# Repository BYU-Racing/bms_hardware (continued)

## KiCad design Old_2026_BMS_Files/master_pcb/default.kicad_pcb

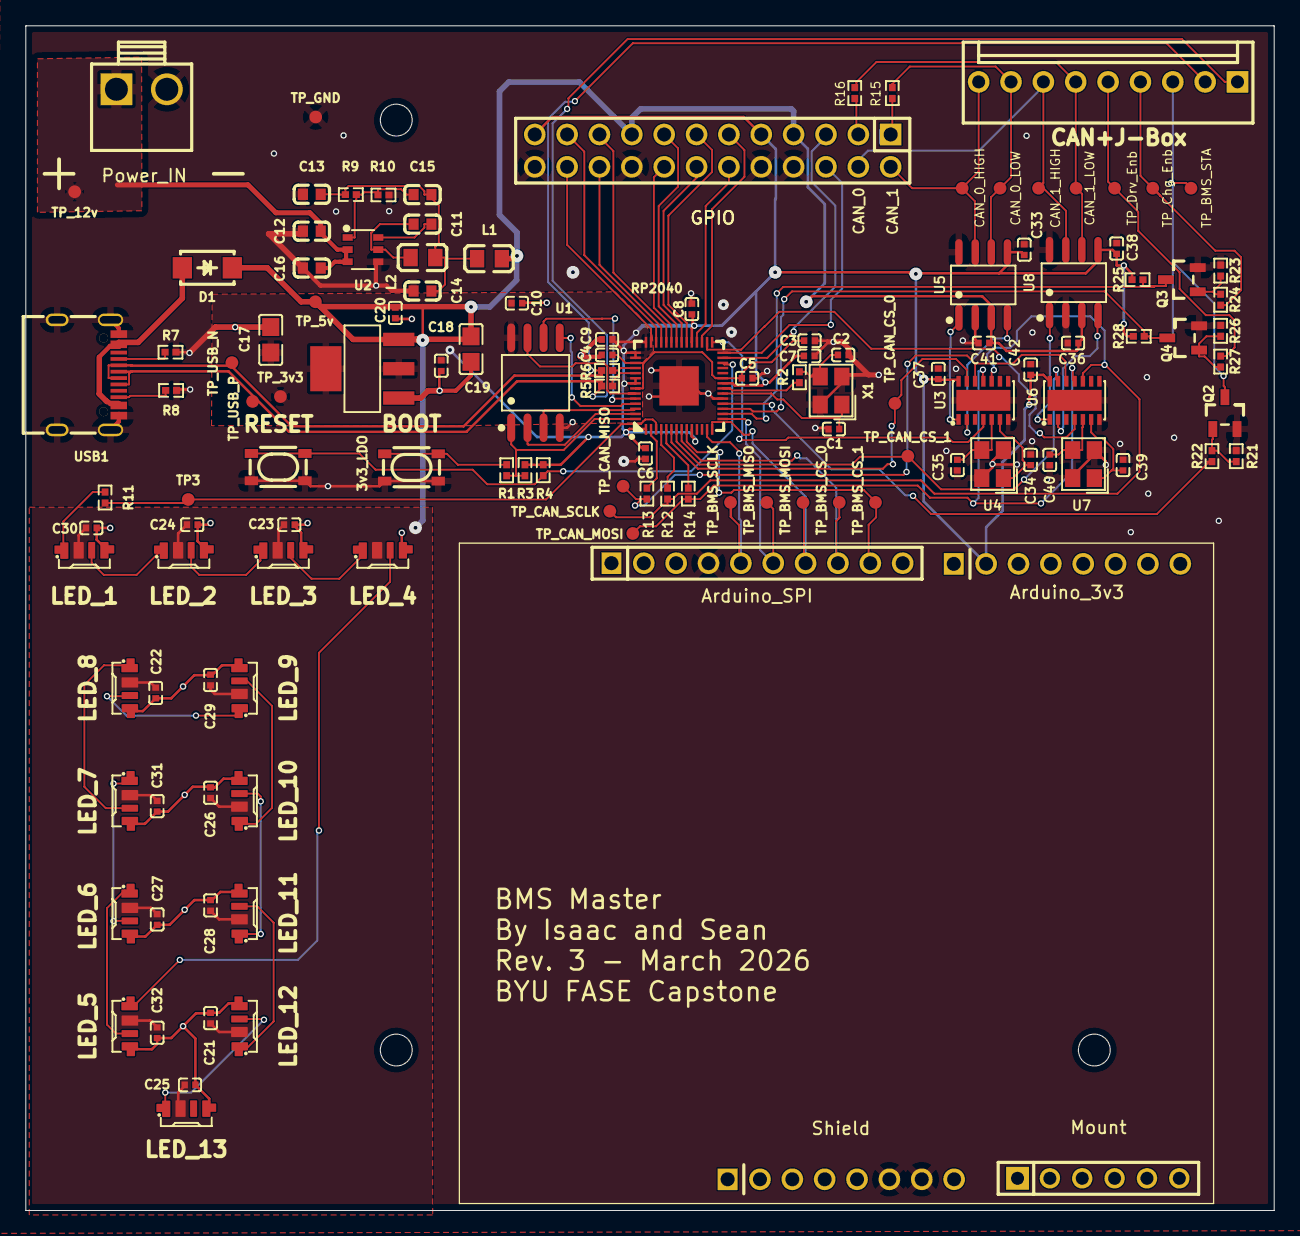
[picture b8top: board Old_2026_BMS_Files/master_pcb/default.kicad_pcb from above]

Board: 2 copper layers, 98.0 x 93.0 mm, 130 parts (0 on the bottom side), 91 nets.

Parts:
3v3_LDO: SOT-223_L6.5-W3.5-P2.30-LS7.0-BR
Arduino_3v3: HDR-TH_8P-P2.54-V-F
Arduino_SPI: HDR-TH_10P-P2.54-V-F
BOOT: KEY-SMD_4P-L4.2-W3.2-P2.20-LS4.6
C1, C2, C34, C35, C39, C40: 22pF ±5% 50V C0G; C0402
C3, C4, C5, C6, C7, C8, C9, C10: 1µF ±10% 25V X5R; C0402
C11, C16: 100nF ±10% 50V X7R; C0603
C12: 10µF ±10% 10V X5R; C0603
C13, C14: 22µF ±20% 6.3V X5R; C0603
C15: 47pF ±5% 50V C0G; C0603
C17, C19: 10µF ±10% 25V X5R; C0805
C18, C20, C21, C22, C23, C24, C25, C26, C27, C28, C29, C30, C31, C32, C33, C36, C37, C38, C41, C42: 100nF ±10% 16V X7R; C0402
CAN+J-Box: CONN-TH_9P-P2.54_MOLEX_22232091
CAN_0_HIGH, CAN_0_LOW, CAN_1_HIGH, CAN_1_LOW: TestPoint_Pad_D1.0mm
D1: SMA_L4.2-W2.6-LS5.0-RD_1
GPIO: HDR-TH_24P-P2.54-V-M-R2-C12-S2.54
L1: L0805
L2: 6.8µH ±20% 550mA 270mΩ; L0805
LED_1, LED_2, LED_3, LED_4, LED_5, LED_6, LED_7, LED_8, LED_9, LED_10, LED_11, LED_12, LED_13: LED-SMD_4P-L4.0-W1.6-L
Mount: HDR-TH_6P-P2.54-V-F
Power_IN: CONN-TH_B2P-VH-LF-SN
Q2, Q3, Q4: SOT-23-3_L2.9-W1.3-P1.90-LS2.4-TR
R1, R2: 1kΩ ±1% 62.5mW; R0402
R3, R4, R25, R28: 10kΩ ±1% 62.5mW; R0402
R5, R6: 27Ω ±1% 62.5mW; R0402
R7, R8, R22: 4.7kΩ ±1% 62.5mW; R0402
R9: 158kΩ ±1% 62.5mW; R0402
R10: 30.1kΩ ±1% 62.5mW; R0402
R11: 150Ω ±1% 62.5mW; R0402
R12, R13, R14: 22Ω ±1% 62.5mW; R0402
R15, R16: 120Ω ±1% 62.5mW; R0402
R21, R24, R27: 100kΩ ±1% 62.5mW; R0402
R23, R26: 1MΩ ±1% 62.5mW; R0402
RESET: KEY-SMD_4P-L4.2-W3.2-P2.20-LS4.6
RP2040: LQFN-56_L7.0-W7.0-P0.4-EP
Shield: HDR-TH_8P-P2.54-V-F
TP3: TestPoint_Pad_D1.0mm
TP_3v3, TP_5v, TP_12v: TestPoint_Pad_D1.0mm
TP_BMS_CS_0, TP_BMS_CS_1: TestPoint_Pad_D1.0mm
TP_BMS_MISO: TestPoint_Pad_D1.0mm
TP_BMS_MOSI: TestPoint_Pad_D1.0mm
TP_BMS_SCLK: TestPoint_Pad_D1.0mm
TP_BMS_STA: TestPoint_Pad_D1.0mm
TP_CAN_CS_0, TP_CAN_CS_1: TestPoint_Pad_D1.0mm
TP_CAN_MISO: TestPoint_Pad_D1.0mm
TP_CAN_MOSI: TestPoint_Pad_D1.0mm
TP_CAN_SCLK: TestPoint_Pad_D1.0mm
TP_Chg_Enb: TestPoint_Pad_D1.0mm
TP_Drv_Enb: TestPoint_Pad_D1.0mm
TP_GND: TestPoint_Pad_D1.0mm
TP_USB_N: TestPoint_Pad_D1.0mm
TP_USB_P: TestPoint_Pad_D1.0mm
U1: SOIC-8_L5.3-W5.3-P1.27-LS8.0-BL
U2: TSOT-23-6_L2.9-W1.6-P0.95-LS2.8-BR
U3, U6: VDFN-14_L4.5-W3.0-P0.65-BL-EP
U4, U7: CRYSTAL-SMD_4P-L3.2-W2.5-BL
U5, U8: SOIC-8_L4.9-W3.9-P1.27-LS6.0-BL
USB1: USB-C-SMD_KH-TYPE-C-16P
X1: CRYSTAL-SMD_4P-L3.2-W2.5-BL

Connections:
3V: 3v3_LDO.2, 3v3_LDO.4, Arduino_3v3.2, C6.1, C7.1, C8.1, C9.1, C10.1, C17.1, C18.1, C33.1, C37.1, C38.1, C42.1, GPIO.9, GPIO.23, R3.1, R4.1, R25.1, R28.1, RP2040.1, RP2040.10, RP2040.22, RP2040.33, RP2040.42, RP2040.43, RP2040.44, RP2040.48, RP2040.49, TP_3v3.1, U1.8, U3.14, U5.5, U6.14, U8.5
5V: 3v3_LDO.3, C19.1, C20.1, C21.1, C22.1, C23.1, C24.1, C25.1, C26.1, C27.1, C28.1, C29.1, C30.1, C31.1, C32.1, C36.1, C41.1, D1.1, GPIO.7, GPIO.17, L1.2, LED_1.2, LED_2.2, LED_3.2, LED_4.2, LED_5.2, LED_6.2, LED_7.2, LED_8.2, LED_9.2, LED_10.2, LED_11.2, LED_12.2, LED_13.2, TP_5v.1, U5.3, U8.3
12V: C12.1, C16.1, Power_IN.1, TP_12v.1, U2.2, U2.3
A5: R7.1, USB1.A5
B5: R8.1, USB1.B5
BMS_status: CAN+J-Box.3, Q2.3, TP_BMS_STA.1
BST: C11.1, U2.6
CAN_CS_0: RP2040.6, TP_CAN_CS_0.1, U3.13
CAN_CS_1: RP2040.7, TP_CAN_CS_1.1, U6.13
FB: C15.2, R9.2, R10.1, U2.1
GND: 3v3_LDO.1, Arduino_SPI.4, BOOT.1, BOOT.2, C1.2, C2.2, C3.2, C4.2, C5.2, C6.2, C7.2, C8.2, C9.2, C10.2, C12.2, C13.2, C14.2, C16.2, C17.2, C18.2, C19.2, C20.2, C21.2, C22.2, C23.2, C24.2, C25.2, C26.2, C27.2, C28.2, C29.2, C30.2, C31.2, C32.2, C33.2, C34.2, C35.2, C36.2, C37.2, C38.2, C39.2, C40.2, C41.2, C42.2, GPIO.8, GPIO.10, GPIO.18, GPIO.24, LED_1.4, LED_2.4, LED_3.4, LED_4.4, LED_5.4, LED_6.4, LED_7.4, LED_8.4, LED_9.4, LED_10.4, LED_11.4, LED_12.4, LED_13.4, Power_IN.2, Q2.1, Q3.1, Q4.1, R7.2, R8.2, R10.2, R21.2, R23.2, R26.2, RESET.1, RESET.2, RP2040.19, RP2040.57, Shield.6, Shield.7, TP_GND.1, U1.4, U2.4, U3.7, U3.15, U4.2, U4.4, U5.2, U5.8, U6.7, U6.15, U7.2, U7.4, U8.2, U8.8, USB1.1, USB1.2, USB1.3, USB1.4, USB1.A1, USB1.A12, USB1.B1, USB1.B12, X1.2, X1.4
RX: GPIO.6, RP2040.28
SCL: GPIO.12, RP2040.32
SDA: GPIO.11, RP2040.31
SW: C11.2, L2.1, U2.5
TX: GPIO.5, RP2040.27
TestPoint_LED_DATA-contact: R11.1, RP2040.3, TP3.1
TestPoint_SPI1_CS_0-contact: Arduino_SPI.8, RP2040.8, TP_BMS_CS_0.1
TestPoint_SPI1_CS_1-contact: Arduino_SPI.9, RP2040.9, TP_BMS_CS_1.1
TestPoint_SPI1_MISO-contact: Arduino_SPI.6, RP2040.15, TP_BMS_MISO.1
USB_DM: R6.2, RP2040.46
USB_DP: R5.2, RP2040.47
USB_D_N: CAN+J-Box.2, R6.1, TP_USB_N.1, USB1.A7, USB1.B7
USB_D_P: CAN+J-Box.1, R5.1, TP_USB_P.1, USB1.A6, USB1.B6
XIN: C1.1, RP2040.20, X1.1
XOUT: R2.1, RP2040.21
bms_status_base_pulldown-B: Q2.2, R21.1, R22.2
boot_btn-output: BOOT.3, BOOT.4, R1.1
button-output: R4.2, RESET.3, RESET.4, RP2040.26
c_osc_2-OSC2: C2.1, R2.2, X1.3
can0-OSC1: C34.1, U3.6, U4.1
can0-OSC2: C35.1, U3.5, U4.3
can0-RXCAN: U3.2, U5.4
can0-TXCAN: U3.1, U5.1
can0-nint: RP2040.29, U3.4
can1-OSC1: C39.1, U6.6, U7.1
can1-OSC2: C40.1, U6.5, U7.3
can1-RXCAN: U6.2, U8.4
can1-TXCAN: U6.1, U8.1
can1-nint: RP2040.30, U6.4
can_0_high: CAN+J-Box.9, CAN_0_HIGH.1, GPIO.2, U5.7
can_0_low: CAN+J-Box.8, CAN_0_LOW.1, R15.2, U5.6
can_0_terminator-_1: GPIO.1, R15.1
can_1_high: CAN+J-Box.7, CAN_1_HIGH.1, GPIO.4, U8.7
can_1_low: CAN+J-Box.6, CAN_1_LOW.1, R16.2, U8.6
can_1_terminator-_3: GPIO.3, R16.1
charge_enable: CAN+J-Box.4, R24.1, TP_Chg_Enb.1
charge_enable_base_pulldown-B: Q3.2, R23.1, R24.2
charge_enable_pullup-C: Q3.3, R25.2, RP2040.16
cs: R1.2, R3.2, RP2040.56, U1.1
drive_enable: CAN+J-Box.5, R27.1, TP_Drv_Enb.1
drive_enable_base_pulldown-B: Q4.2, R26.1, R27.2
drive_enable_pullup-C: Q4.3, R28.2, RP2040.17
footprint-DIN-0: LED_1.1, R11.2
footprint-DIN-1: LED_1.3, LED_2.1
footprint-DIN-2: LED_10.3, LED_11.1
footprint-DIN-3: LED_11.3, LED_12.1
footprint-DIN-4: LED_12.3, LED_13.1
footprint-DIN-5: LED_2.3, LED_3.1
footprint-DIN-6: LED_3.3, LED_4.1
footprint-DIN-7: LED_4.3, LED_5.1
footprint-DIN-8: LED_5.3, LED_6.1
footprint-DIN-9: LED_6.3, LED_7.1
footprint-DIN-10: LED_7.3, LED_8.1
footprint-DIN-11: LED_8.3, LED_9.1
footprint-DIN-12: LED_9.3, LED_10.1
gpio0: R13.1, RP2040.2
gpio2: R12.1, RP2040.4
gpio3: R14.1, RP2040.5
gpio15: R22.1, RP2040.18
gpio22: GPIO.13, RP2040.34
gpio23: GPIO.14, RP2040.35
gpio24: GPIO.15, RP2040.36
gpio25: GPIO.16, RP2040.37
gpio26_a0: GPIO.19, RP2040.38
gpio27_a1: GPIO.20, RP2040.39
gpio28_a2: GPIO.21, RP2040.40
gpio29_a3: GPIO.22, RP2040.41
io0: RP2040.53, U1.5
io1: RP2040.55, U1.2
io2: RP2040.54, U1.3
io3: RP2040.51, U1.7
power_1V-VCC: C3.1, C4.1, C5.1, RP2040.23, RP2040.45, RP2040.50
sclk: RP2040.52, U1.6
spi1-MOSI: Arduino_SPI.7, RP2040.14, TP_BMS_MOSI.1
spi1-SCLK: Arduino_SPI.5, RP2040.13, TP_BMS_SCLK.1
spi-MISO: R13.2, TP_CAN_MISO.1, U3.12, U6.12
spi-MOSI: R14.2, TP_CAN_MOSI.1, U3.11, U6.11
spi-SCLK: R12.2, TP_CAN_SCLK.1, U3.10, U6.10
usb_vbus-VCC: D1.2, USB1.A4, USB1.A9, USB1.B4, USB1.B9
vout_sw-VCC: C13.1, C14.1, C15.1, L1.1, L2.2, R9.1
